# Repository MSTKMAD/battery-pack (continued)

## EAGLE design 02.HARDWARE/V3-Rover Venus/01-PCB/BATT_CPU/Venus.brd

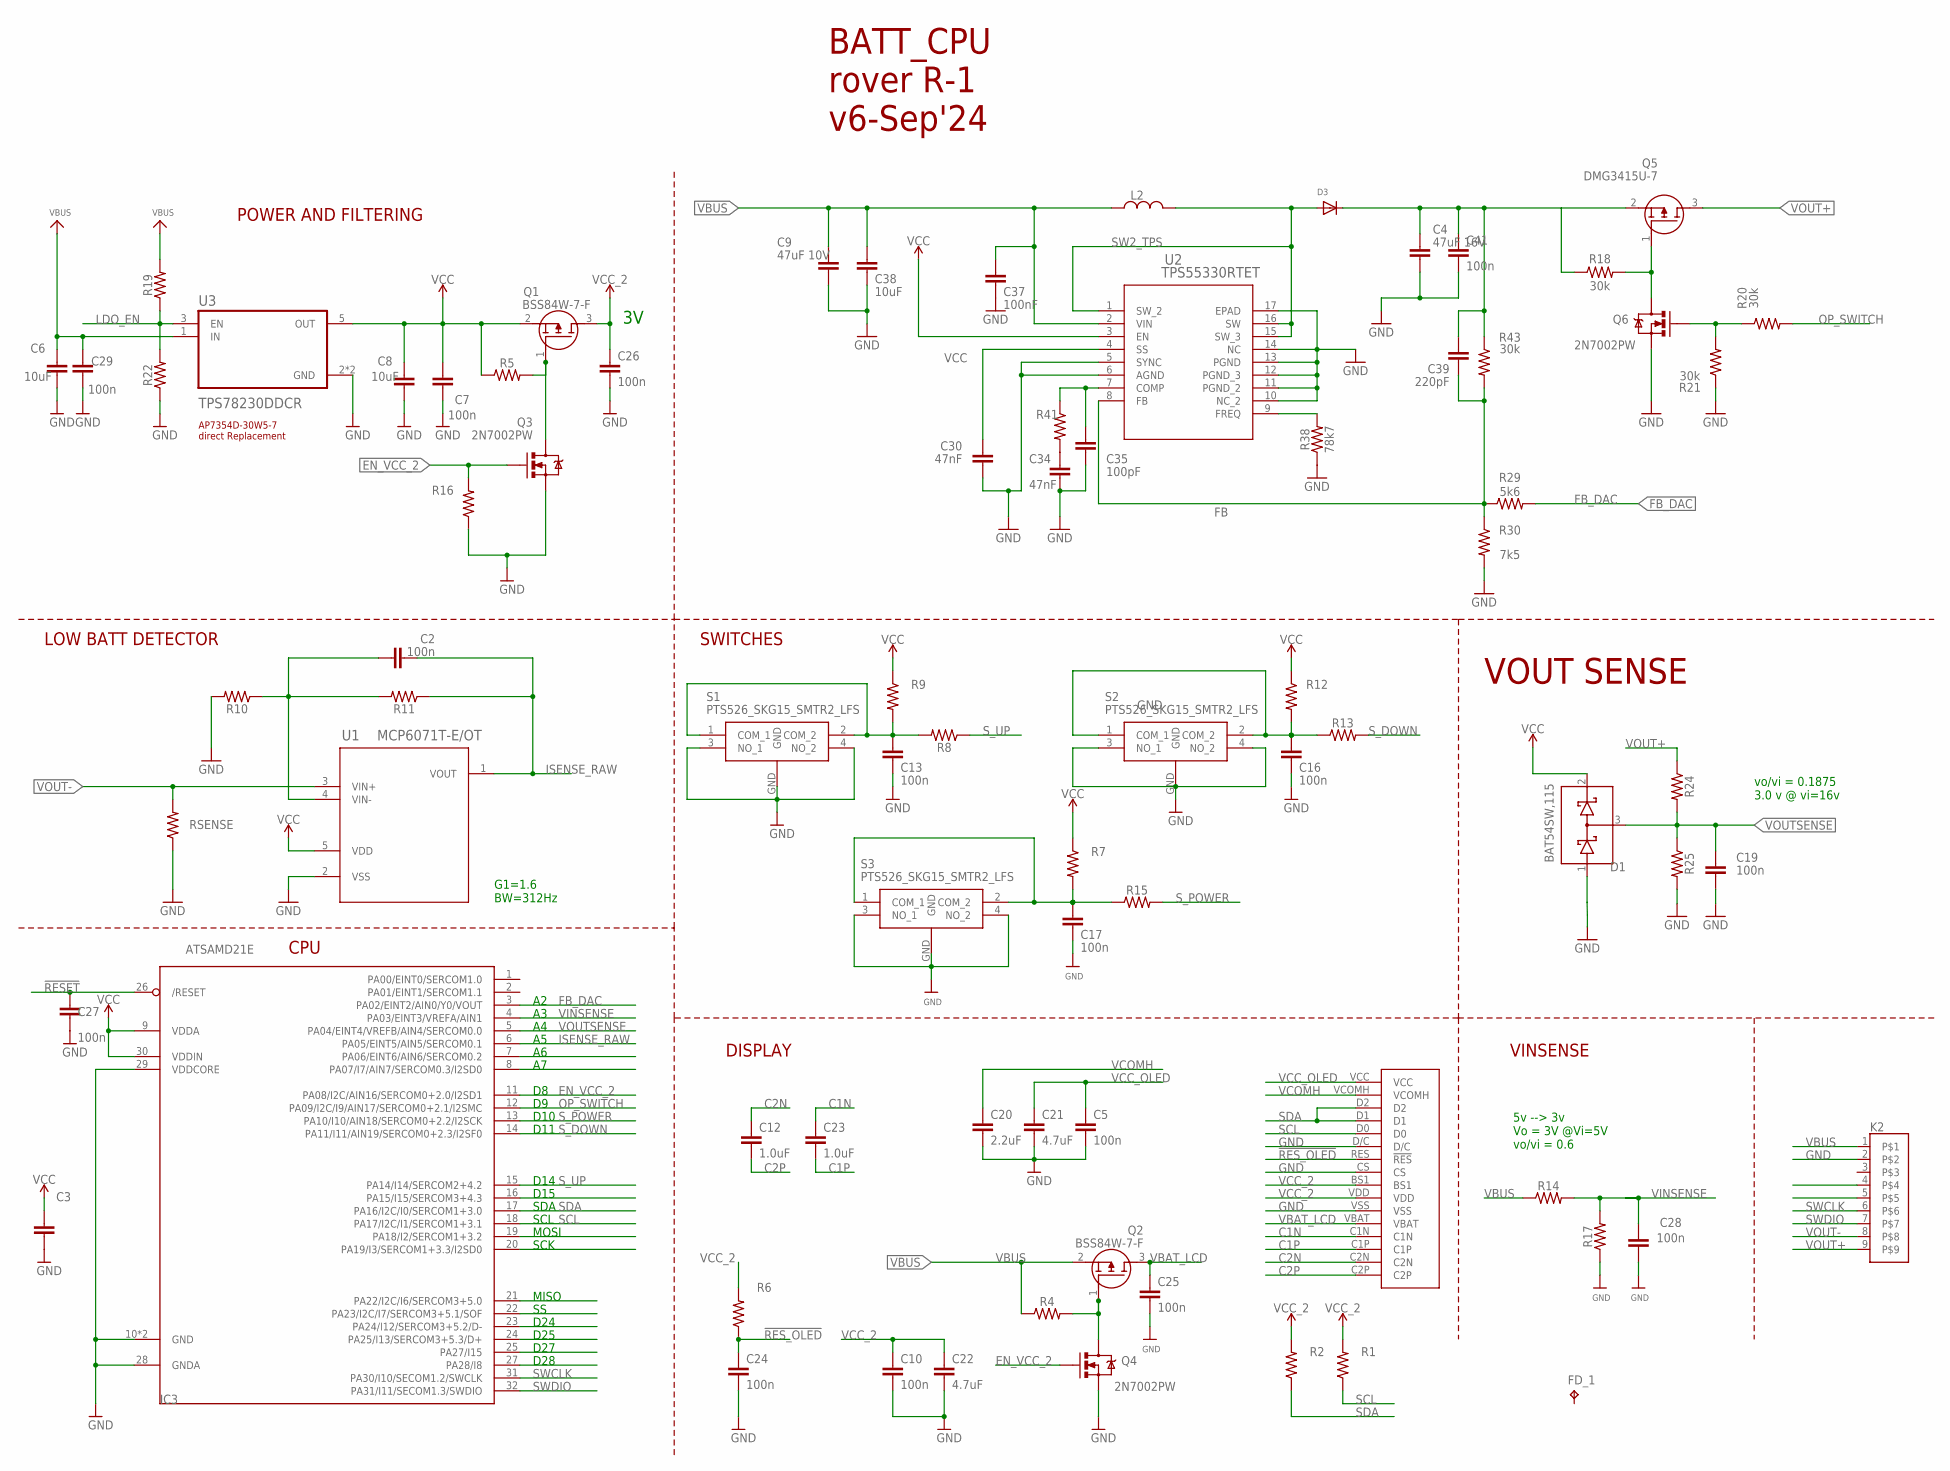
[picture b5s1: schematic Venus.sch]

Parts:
C2, C19, C41: 100n; 0603
C3, C5, C7, C10, C13, C16, C17, C24, C25, C26, C27, C28, C29: 100n; 0402
C4: 47uF 16V; CAPC3216X135
C6, C8: 10uF; 0603
C9: 47uF 10V; CAPC2012X110
C12, C23: 1.0uF; 0402
C20: 2.2uF; 0603
C21, C22: 4.7uF; 0603
C30, C34: 47nF; 0603
C35: 100pF; 0603
C37: 100nF; 0603
C38: 10uF; 0805
C39: 220pF; 0603
D1: BAT54SW,115; SOT65P210X110-3N
D3: DIODESOD-123; SOD-123
FD_1: FD_1; TP06SQ
IC3: ATSAMD21E; QFN32_5MM
K2: FLEX9_2MM
L2: L_CHIP-1206(3216-METRIC); INDC3216X190
Q1, Q2: BSS84W-7-F; SOT65P222X110-3N
Q3, Q4, Q6: 2N7002PW; SOT323
Q5: DMG3415U-7; SSM3J332RLFT
R1, R2, R4, R5, R6, R7, R8, R9, R10, R11, R12, R13, R14, R15, R16, R17, R19, R22, R24, R25, R41: 0402
R18, R20, R21, R43: 30k; 0402
R29: 5k6; 0402
R30: 7k5; 0402
R38: 78k7; 0402
RSENSE: 1206
S1, S2, S3: PTS526_SKG15_SMTR2_LFS; PTS526SKG15SMTR2LFS
U1: MCP6071T-E/OT; SOT-23-5_MC_MCH
U2: TPS55330RTET; RTE16_1P66X1P66_TEX
U3: TPS78230DDCR; SOT95P280X110-5N
U$30: 72X40_OLED; LCD_16_PINS

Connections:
!RESET: C27.1, IC3.26 (/RESET)
!RES_OLED: C24.1, R6.1, U$30.RES (!RES)
C1N: C23.1, U$30.C1N
C1P: C23.2, U$30.C1P
C2N: C12.1, U$30.C2N
C2P: C12.2, U$30.C2P
COMP_TPS: C35.2, R41.1, U2.7 (COMP)
EN_VCC_2: IC3.11 (PA08/I2C/AIN16/SERCOM0+2.0/I2SD1), Q3.1 (G), Q4.1 (G), R16.2
FB: C39.1, R29.1, R30.1, R43.2, U2.8 (FB)
FB_DAC: IC3.3 (PA02/EINT2/AIN0/Y0/VOUT), R29.2
FREQ_TPS: R38.2, U2.9 (FREQ)
GND: C3.2, C4.2, C5.2, C6.2, C7.2, C8.2, C9.2, C10.2, C13.2, C16.2, C17.2, C19.2, C20.2, C21.2, C22.2, C24.2, C25.2, C26.2, C27.2, C28.2, C29.2, C30.2, C34.1, C35.1, C37.1, C38.1, C41.2, D1.1 (A), IC3.10 (GND), IC3.28 (GNDA), IC3.29 (VDDCORE), IC3.33 (GND), K2.2, Q3.2 (S), Q4.2 (S), Q6.2 (S), R10.2, R16.1, R17.1, R21.1, R22.1, R25.2, R30.2, R38.1, RSENSE.1, S1.3 (NO_1), S1.4 (NO_2), S1.GND, S2.3 (NO_1), S2.4 (NO_2), S2.GND, S3.3 (NO_1), S3.4 (NO_2), S3.GND, U1.2 (VSS), U2.5 (SYNC), U2.6 (AGND), U2.10 (NC_2), U2.11 (PGND_2), U2.12 (PGND_3), U2.13 (PGND), U2.14 (NC), U2.17 (EPAD), U3.2 (GND), U3.4 (GND), U$30.CS, U$30.D/C, U$30.VSS
ISENSE_RAW: C2.1, IC3.6 (PA05/EINT5/AIN5/SERCOM0.1), R11.1, U1.1 (VOUT)
LDO_EN: R19.1, R22.2, U3.3 (EN)
unnamed: C17.1, R7.2, R15.1, S3.1 (COM_1), S3.2 (COM_2)
unnamed: C13.1, R8.2, R9.2, S1.1 (COM_1), S1.2 (COM_2)
unnamed: C16.1, R12.2, R13.1, S2.1 (COM_1), S2.2 (COM_2)
unnamed: Q2.1 (G), Q4.3 (D), R4.2
unnamed: C2.2, R10.1, R11.2, U1.4 (VIN-)
unnamed: Q1.1 (G), Q3.3 (D), R5.2
unnamed: Q6.1 (G), R20.1, R21.2
unnamed: Q5.1 (G), Q6.3 (D), R18.2
unnamed: C30.1, U2.4 (SS)
unnamed: C34.2, R41.2
OP_SWITCH: IC3.12 (PA09/I2C/I9/AIN17/SERCOM0+2.1/I2SMC), R20.2
SCL: IC3.18 (PA17/I2C/I1/SERCOM1+3.1), R1.1, U$30.D0
SDA: IC3.17 (PA16/I2C/I0/SERCOM1+3.0), R2.1, U$30.D1, U$30.D2
SW2_TPS: D3.A, L2.2, U2.1 (SW_2), U2.15 (SW_3), U2.16 (SW)
SWCLK: IC3.31 (PA30/I10/SECOM1.2/SWCLK), K2.6
SWDIO: IC3.32 (PA31/I11/SECOM1.3/SWDIO), K2.7
S_DOWN: IC3.14 (PA11/I11/AIN19/SERCOM0+2.3/I2SF0), R13.2
S_POWER: IC3.13 (PA10/I10/AIN18/SERCOM0+2.2/I2SCK), R15.2
S_UP: IC3.15 (PA14/I14/SERCOM2+4.2), R8.1
VBAT_LCD: C25.1, Q2.3 (D), U$30.VBAT
VBUS: C6.1, C9.1, C29.1, C37.2, C38.2, K2.1, L2.1, Q2.2 (S), R4.1, R14.1, R19.2, U2.2 (VIN), U3.1 (IN)
VCC: C3.1, C7.1, C8.1, D1.2 (C), IC3.9 (VDDA), IC3.30 (VDDIN), Q1.2 (S), R5.1, R7.1, R9.1, R12.1, U1.5 (VDD), U2.3 (EN), U3.5 (OUT)
VCC_2: C10.1, C22.1, C26.1, Q1.3 (D), R1.2, R2.2, R6.2, U$30.BS1, U$30.VDD
VCC_OLED: C5.1, C21.1, U$30.VCC
VCOMH: C20.1, U$30.VCOMH
VINSENSE: C28.1, IC3.4 (PA03/EINT3/VREFA/AIN1), R14.2, R17.2
VOUT+: K2.9, Q5.3 (D), R24.1
VOUT-: K2.8, RSENSE.2, U1.3 (VIN+)
VOUTSENSE: C19.1, D1.3 (A-C), IC3.5 (PA04/EINT4/VREFB/AIN4/SERCOM0.0), R24.2, R25.1
VSOURCE: C4.1, C39.2, C41.1, D3.C, Q5.2 (S), R18.1, R43.1

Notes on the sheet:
POWER AND FILTERING
AP7354D-30W5-7 direct Replacement
LOW BATT DETECTOR
CPU
D15
5v --> 3v Vo = 3V @Vi=5V vo/vi = 0.6
BATT_CPU rover R-1 v6-Sep'24
DISPLAY
SWITCHES
VINSENSE
G1=1.6 BW=312Hz
vo/vi = 0.1875 3.0 v @ vi=16v
VOUT SENSE
SDA
SCL
MOSI
SCK
D14
MISO
D24
D25
D27
D28
D10
D11

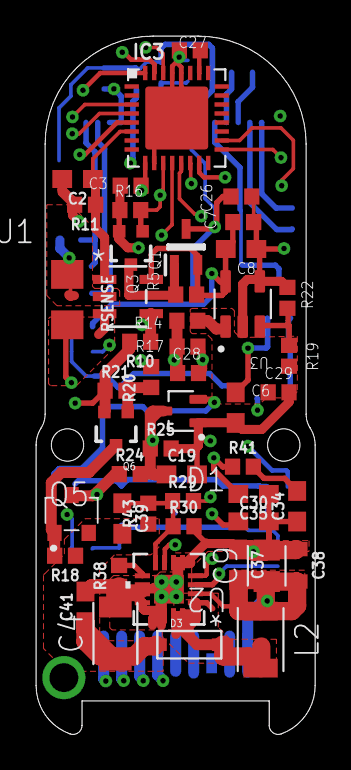
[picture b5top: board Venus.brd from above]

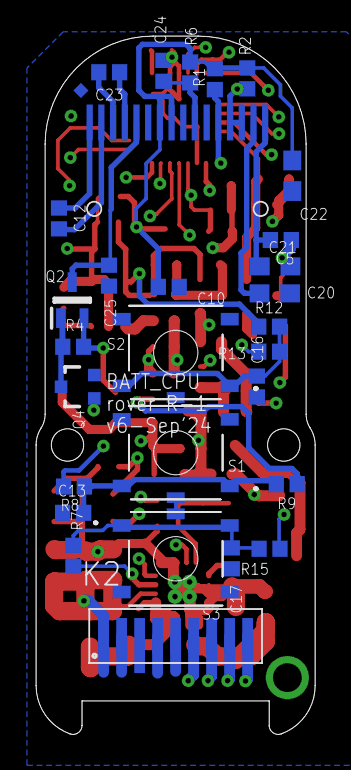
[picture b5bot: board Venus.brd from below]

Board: 4 copper layers, 15.5 x 38.8 mm, 79 parts (30 on the bottom side), 44 nets.

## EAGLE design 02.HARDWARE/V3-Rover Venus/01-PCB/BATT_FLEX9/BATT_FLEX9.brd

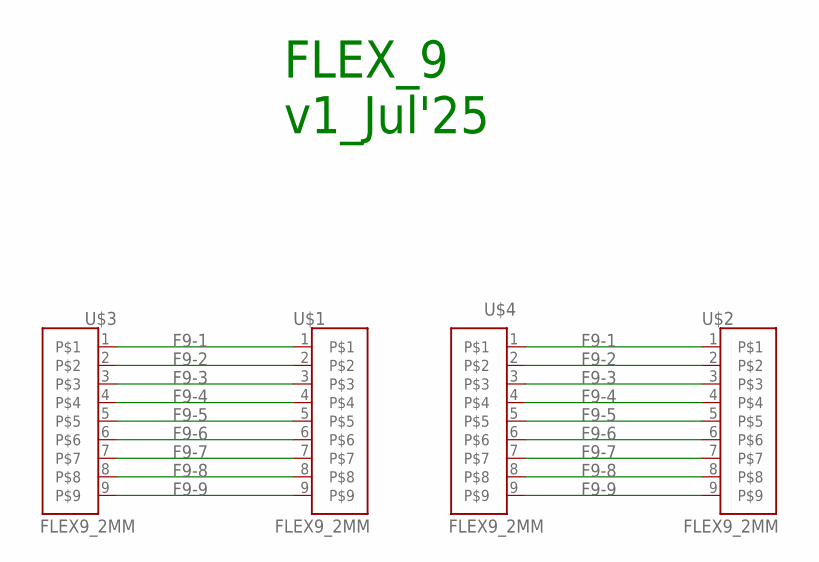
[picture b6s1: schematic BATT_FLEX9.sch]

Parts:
U$1, U$2, U$3, U$4: FLEX9_2MM

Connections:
F9-1: U$1.1, U$2.1, U$3.1, U$4.1
F9-2: U$1.2, U$2.2, U$3.2, U$4.2
F9-3: U$1.3, U$2.3, U$3.3, U$4.3
F9-4: U$1.4, U$2.4, U$3.4, U$4.4
F9-5: U$1.5, U$2.5, U$3.5, U$4.5
F9-6: U$1.6, U$2.6, U$3.6, U$4.6
F9-7: U$1.7, U$2.7, U$3.7, U$4.7
F9-8: U$1.8, U$2.8, U$3.8, U$4.8
F9-9: U$1.9, U$2.9, U$3.9, U$4.9

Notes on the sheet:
FLEX_9 v1_Jul'25

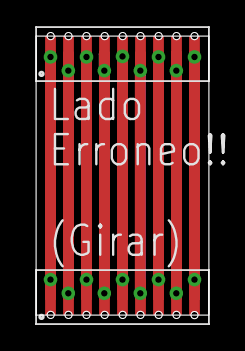
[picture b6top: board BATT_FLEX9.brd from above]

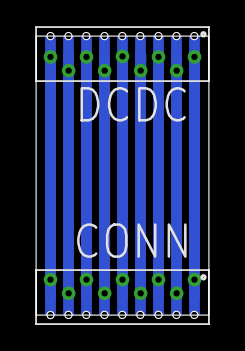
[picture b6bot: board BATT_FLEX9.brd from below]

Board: 2 copper layers, 9.6 x 15.5 mm, 4 parts (2 on the bottom side), 9 nets.

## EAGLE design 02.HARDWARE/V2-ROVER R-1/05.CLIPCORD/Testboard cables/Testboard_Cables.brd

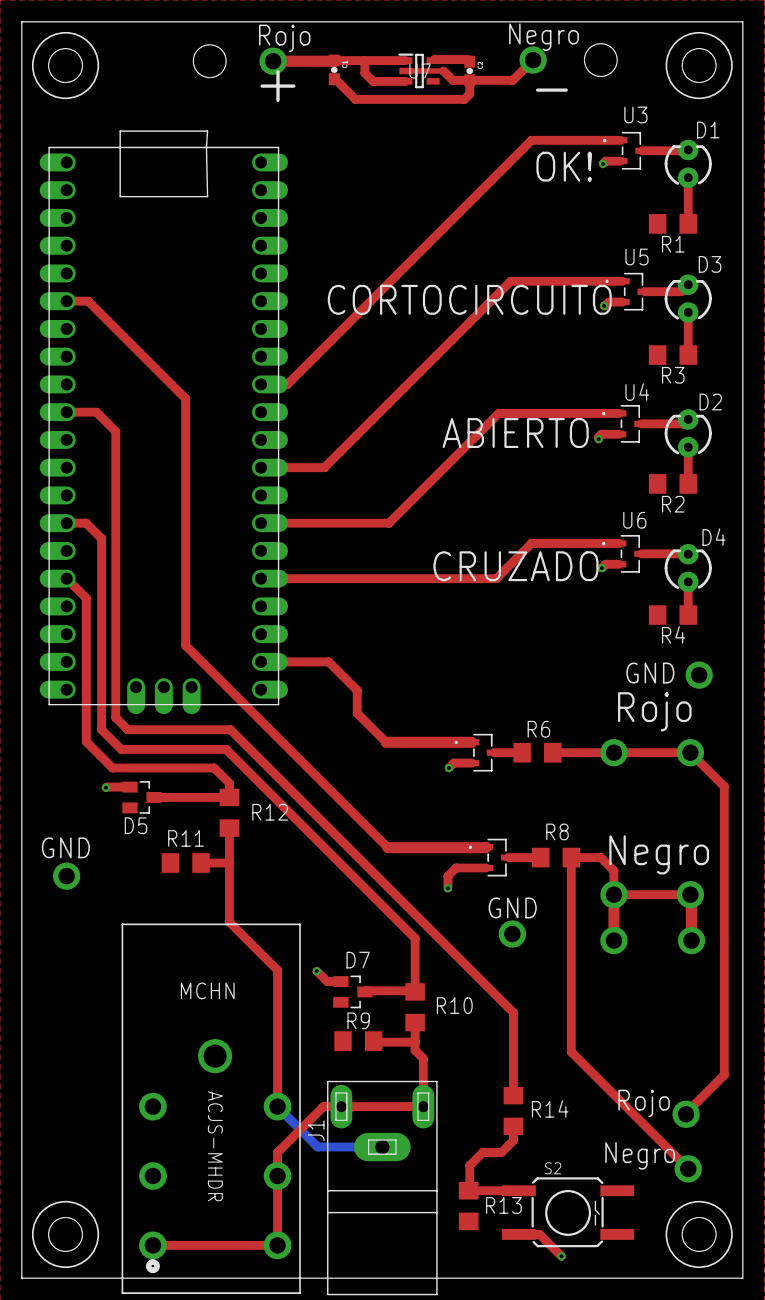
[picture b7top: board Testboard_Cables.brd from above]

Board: 2 copper layers, 65.9 x 114.9 mm, 31 parts (0 on the bottom side), 25 nets.

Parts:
C1: 2.2u; 0603-CAP
C2: 47uF 6.3V; 0603-CAP
D1, D2, D3, D4: LED_3MM
D5, D7: BAV199; SOT23
J1: PJRAN1X1U01X
MCHN: ACJS-MHDR; CONN_MHDR_AMP
R1, R2, R3, R4: 150R; 1206
R6, R8, R10, R12, R14: 100R; 1206
R9, R11, R13: 1k; 1206
S2: TAC_SW_SMD_KSC931G
U1, U2, U3, U4, U5, U6: MMUN2211LT1G; SOT-23-3_1P4X3P040_ONS
U7: AP2205-33W5-7; SOT95P282X145-5N
X1: RPI_PICO_TH

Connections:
A: U1.1, X1.GP17
B: U2.1, X1.GP4
BUTTON: R14.1, X1.GP7
CROSSED: U6.1, X1.GP19
GND: C1.2, C2.2, D5.1, D7.1, S2.3, U1.2, U2.2, U3.2, U4.2, U5.2, U6.2, U7.2, X1.GND@1, X1.GND@2, X1.GND@3, X1.GND@4, X1.GND@5, X1.GND@6, X1.GND@7, X1.GND@8
INA: J1.2, J1.3, MCHN.1, MCHN.4, MCHN.5, R9.2, R10.1
INB: J1.1, MCHN.6, R11.2, R12.1
INPUT: C1.1, U7.1, U7.3
unnamed: D1.K, U3.3
unnamed: D1.A, R1.1
unnamed: R13.1, R14.2, S2.1
unnamed: D2.K, U4.3
unnamed: D2.A, R2.1
unnamed: D3.K, U5.3
unnamed: D3.A, R3.1
unnamed: D4.K, U6.3
unnamed: D4.A, R4.1
unnamed: R6.2, U1.3
unnamed: R8.2, U2.3
OK: U3.1, X1.GP27_A1
OPEN: U4.1, X1.GP21
RA: D7.3, R10.2, X1.GP10
RB: D5.3, R12.2, X1.GP12
SHT_CRT: U5.1, X1.GP22
VCC: C2.1, D5.2, D7.2, R1.2, R2.2, R3.2, R4.2, R9.1, R11.1, R13.2, U7.5, X1.VSYS

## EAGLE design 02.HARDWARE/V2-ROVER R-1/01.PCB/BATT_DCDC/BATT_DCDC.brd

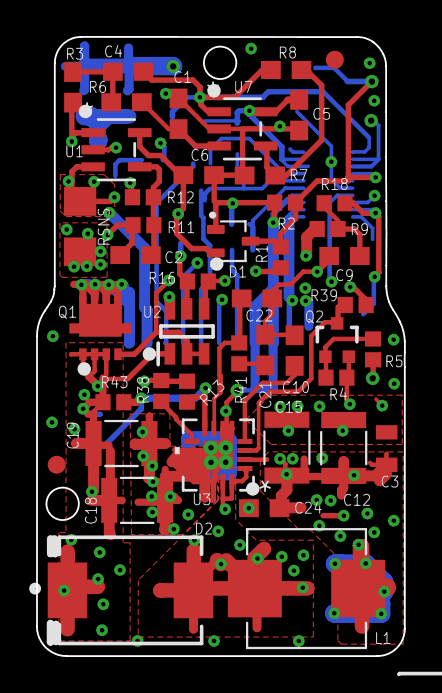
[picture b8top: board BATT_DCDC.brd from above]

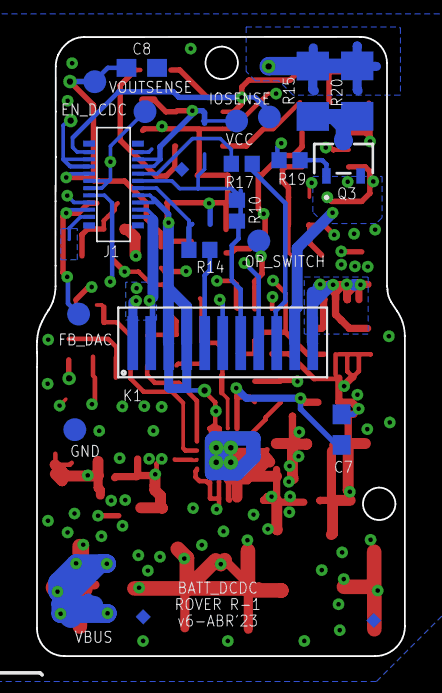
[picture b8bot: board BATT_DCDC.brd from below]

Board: 4 copper layers, 20.4 x 34.4 mm, 67 parts (22 on the bottom side), 36 nets.

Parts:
C1, C4: 1u; 0603-NO
C2, C5, C6, C8: 100n; 0603
C3: 10uF; 0805
C7: 220pF; 0603
C9: N.A.; 0603
C10, C21: 47nF; 0603
C12, C15: 47uF 16V; WCAP-CSGP_1210
C18, C19: 47uF 25V; WCAP-CSGP_1210
C22: 100pF; 0603
C24: 100nF; 0603
D1: BAT54SW,115; SOT65P210X110-3N
D2: B520C-13-F; DIOM7959X250N
EN_DCDC: TESTPAD_TPSQB1,27; TESTPAD_B1,27
FB_DAC: TESTPAD_TPSQB1,27; TESTPAD_B1,27
FD_1, FD_2, FD_3: FD_1; TP06SQ
GND: TESTPAD_TPSQB1,27; TESTPAD_B1,27
IOSENSE: TESTPAD_TPSQB1,27; TESTPAD_B1,27
J1: DF40C-20DP-0.4V_51_; DF40C-20DPA
K1: FLEX11
L1: 2.2uH - 74437346022; INDM7366X500
OP_SWITCH: TESTPAD_TPSQB1,27; TESTPAD_B1,27
Q1: NVTFS9D6P04M8LTAG; NVTFS5124PLTWG
Q2: 2N7002PW; SOT323
Q3: DMN3023L-7; SOT23-TO-236AB_NEX-L
R1: 169k; 0402
R2: 39k; 0402
R3: 2k4; 0603
R4: 100k; 0402
R5, R19: 33R; 0402
R6: 62k; 0603
R7: 4k3; 0603
R8: 36k; 0603
R9: 5k6; 0402
R10, R14, R17: 100R; 0402
R11: 5k1; 0402
R12: 8k2; 0402
R13: 7k5; 0402
R15, R20: 10R; 1206
R16: 10k; 0402
R18: 0R; 0402
R38, R39: 78k7; 0402
R41: 15k; 0402
R43: 30k; 0402
RSNS: 100mR; 1206
U1, U7: MCP6071T-E/OT; SOT-23-5_MC_MCH
U2: LM5114BMF_NOPB; SOT95P280X145-6N
U3: TPS55330RTET; RTE16_1P66X1P66_TEX
U$1, U$2: FIDUCIAL""; FIDUCIAL_1MM
VBUS: TESTPAD_TPSQB1,27; TESTPAD_B1,27
VCC: TESTPAD_TPSQB1,27; TESTPAD_B1,27
VOUTSENSE: TESTPAD_TPSQB1,27; TESTPAD_B1,27

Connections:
!RESET: J1.8, R17.1
COMP_TPS: C22.2, R41.1, U3.7
EN_DCDC: EN_DCDC.TP, J1.9, J1.11, R5.2
EN_TPS: Q2.3, R39.2, U3.3
FB: C7.1, R9.1, R13.1, R43.2, U3.8
FB_DAC: FB_DAC.TP, J1.17, R18.2
FREQ_TPS: R38.2, U3.9
GND: C1.2, C3.1, C5.2, C6.2, C8.2, C9.2, C10.2, C12.1, C15.1, C18.1, C19.1, C21.1, C22.1, C24.1, D1.1, GND.TP, J1.2, J1.14, J1.16, K1.3, K1.4, Q2.2, R2.2, R4.1, R7.2, R12.2, R13.2, R16.2, R38.1, RSNS.1, U1.2, U2.4, U3.5, U3.6, U3.10, U3.11, U3.12, U3.13, U3.14, U3.17, U7.2
IOSENSE: C4.2, IOSENSE.TP, J1.1, R8.1, U7.1
ISENSE_RAW: C2.1, R3.2, R11.1, U1.1
unnamed: C2.2, R11.2, R12.1, U1.4
unnamed: R7.1, R8.2, U7.4
unnamed: C4.1, R3.1, R6.2
unnamed: Q2.1, R4.2, R5.1
unnamed: C1.1, R6.1, U7.3
unnamed: K1.8, R10.2
unnamed: Q3.3, R15.1, R20.1
unnamed: Q1.4, R19.1, U2.2, U2.3
unnamed: K1.10, R17.2
unnamed: K1.5, R14.2
unnamed: C9.1, R9.2, R18.1
unnamed: Q3.1, R19.2
unnamed: C10.1, U3.4
unnamed: C21.2, R41.2
OP_SWITCH: J1.3, J1.5, OP_SWITCH.TP, R16.1, U2.5
RXI: J1.15, K1.9
SW2_TPS: D2.A, L1.2, U3.1, U3.15, U3.16
SWCLK: J1.10, R10.1; also elsewhere on the board
SWDIO: J1.12, R14.1; also elsewhere on the board
TXO: J1.13, K1.7
VBUS: C3.2, C12.2, C15.2, C24.2, J1.18, J1.20, K1.1, K1.2, L1.1, U3.2, VBUS.TP
VCC: C5.1, C6.1, D1.2, J1.4, J1.6, R39.1, U1.5, U7.5, VCC.TP; also elsewhere on the board
VOUT+: K1.12, Q1.5, Q1.6, Q1.7, Q1.8, Q1.9, Q1.10, Q1.11, R1.1, R15.2, R20.2
VOUT-: K1.11, Q3.2, RSNS.2, U1.3
VOUTSENSE: C8.1, D1.3, J1.7, R1.2, R2.1, VOUTSENSE.TP
VSOURCE: C7.2, C18.2, C19.2, D2.C, Q1.1, Q1.2, Q1.3, R43.1, U2.1, U2.6

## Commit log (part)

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2023-01-27 Ajuste del Debug via puerto Serie
2023-01-27 Fix del timer del boton central en la interrupcion del despertar.
2023-01-27 enviado a PCBWAY
2023-01-27 close #29
2023-01-31 Test de los avisos de los errores
2023-01-31 codigo de verificacion de fabricacion de las placas de testeo.
2023-02-01 Calculo de los valores del DAC de 12 bits
2023-02-01 Mensajes de aviso de errores. close #31
2023-02-09 Añadimos el clip de thunder al repositorio
2023-02-10 Version 1 PCB JACK
2023-02-15 Close issue #33
    Nuevo diseño para conector de Amphenol
2023-02-20 codigo de testeo para la fase de produccion version 1
2023-02-24 Cierra el issue #38
    Pin de VO+ desplazado
2023-02-27 close #36
2023-02-27 close #35
2023-03-06 Funcion de Debugg
2023-03-06 close #34
2023-03-06 Test Mode. Actualizacion de la EEPROM
2023-03-17 Close #43
2023-03-17 Ajuste del umbral de la proteccion de cortocircuito
    tras realizar una serie de pruebas se decide bajar de 3A a 1,9A.
    Al realizar un corto franco se observa que la batería mide cerca de 2A.
2023-03-17 Close #40
2023-03-17 Ajuste del modo test.
    - Corrección de la salida del modo test para que todos los flags tengan el valor correcto.
    - Se añade comprobación del sensado de corriente y voltaje por pantalla,
    - Modificación de las velocidades de los trenes de pulso del Enable y del OP swtich.
2023-03-17 Cambio de nombre de la Bom del sistema
2023-03-17 Actualizacion parcial de librerias
2023-03-17 documentación de Testeo
2023-03-17 Auto stash before rebase of "refs/heads/develop"
2023-03-21 Cambio de dinamico a fijo los valores de sensado druante el test
    Para poder realizar un logeo claro y sencillo se decide que una vez se realice la verificación, el valor se quede estático.
    Adicionalmente se aumentan las variables de uint16 a uin32 para evitar el rebosamiento durante la verificación.
2023-03-21 Close #45
    Se detecta el fallo al intentar comunicarse por I2C con la pantalla cuando esta no esta correctamente alimentada tras el despertar.
    Se incluye una inicialización al despertar.
2023-03-22 Incorporacion de carpeta GFX modificada
2023-04-10 Ajuste de la posicion del numeo de serie en memoria
2023-04-12 Close #37
2023-04-13 Ajuste del incremento del modo boost
    Se decide ajustar a 0.3v el aumento que supone el modo boost.
    La linea de tensión en mas corta que en la MK y por tanto no es necesario un incremento tan grane
2023-04-17 Ajuste del WachtDog en el Naming
2023-04-25 Correccion protecciones close#44
    Se decide modificar el funcionamiento de las protecciones para ajustar al ciclo de programa y controlar los tiempos desde la construcción del Health Monitor exclusivamente.
2023-04-25 Libreria de Memoria RAM
2023-04-25 Inclusion del puerto serie en alguos puntos
    Se cierra el puerto serie para agilizar el ciclo de programa
2023-04-25 Close #51
2023-04-25 Close #24
2023-05-02 Cambio del control de tiempo de activacion del LOW BATT
2023-05-05 Close #55
    Solucion del error por Undervoltage.
2023-05-16 Introducción de Supervisor de tensión con control de RESET 2,63.
2023-05-16 Inclusion de Tests Pads
2023-05-16 Serigrafia de version 3
2023-05-16 Actualizacion BOM v6
2023-05-16 Cambio en el encapsulado de 4 Resistencias para evitar que salten en el soldado.
2023-05-16 Produccion 2 - Mecanica
    Actualizacion de la ficheros de mecanica para la segunda produccion
2023-05-17 v7
    Issue #49, #59, #60 y #63
2023-05-17 Cierra issue #63 #59 #49 #32 #60
2023-05-18 SETI Batch_2
    Generacion de GERBER
    Generacion de MOUNTSMD Files
2023-05-18 fichero movido a GERBER directory
2023-05-18 HISTORY updated
2023-05-18 Se crea el folder de PRODUCCION
    para tener identificado todos los ficheros enviados a proveedores y fabricantes
2023-06-01 Fix Errors.
    Errores en los condensadores. C2 por C6.
    Errores en R20 y R21. Los valores estaban intercambiados.
2023-06-01 Diseño Clipcord PCB
2023-06-01 Tabla potencia-tiempo
2023-06-22 Correcion de la granularidad del power use
2023-08-02 Ajuste de tiempos del test DCDC
2023-08-02 Modo Nitro version inicial
2023-08-02 Stop Tracking Produccion folder
2023-08-03 Fix values en Test DCDC
    Ajuste de los valores de verificacion de corriente en el Test 3 de la DCDC
2023-08-21 primera version
2023-08-21 Enviado a Adam Darklord
    Util para post o para demostraciones
2023-08-24 se cambia la forma exterior (WIP)
    No esta terminado
2023-08-25 Placa de Conexiones DCDC Pogo v2 + Placas Pinza
2023-08-25 PCBs Testbench DK Motor+Optos
2023-09-02 Pedido JLCJBC - 1er Pedido
2023-09-05 Cambios en libreria DCDC y adaptacion del codigo B2 al uso de PWM
    Se incluyen las carpetas de testeo y de codigos de ejemplo. Ademas de la libreria usada
2023-09-11 Issue #72
2023-09-19 Cambio del Nitro.
    El nitro por encima de 5v es una escalera hasta 4 voltios por encima del voltaje objetivo.
2023-09-20 Commit anused PIN.
2023-09-20 Adaptacion placa CONECTORES a Universal
2023-09-21 Cambios menores antes de pedido
2023-09-21 Cambios menores antes de pedido + GERBER
2023-09-21 Cambios menores en esquematico
    Se corrigen valores de Resistencias para PWM
    Actualizado el titulo del esquematico
    Limpieza general
2023-09-21 GERBER para pedido SETI
2023-09-22 Codigo principal recuperado
2023-09-25 Revisión BOM previa envio SETI
2023-09-26 Fix error
    Solucion de inconsistencia de valores entre el BRD y el SCH
2023-09-26 Revision antes de enviar a SETI 3ra produccion
    Se actuliza la columna NEW
2023-09-26 Revision antes de envio SETI 3ra produccion - SEP-23
2023-09-26 Cambio de diseño de las placas de la univerasl
    v2
2023-09-26 Ajuste del ancho del orificio del pogo
2023-09-29 Modificaciones en area de soldadura para que haya mas superficie (WIP)
2023-09-29 Revert "Activacion del Nitro Por defecto"
    This reverts commit 9dda1e81689fddb32595ea665b642b7bc7b6e64d.
2023-10-02 Modificacion v3 Pogo pin universal
2023-10-04 Produccion de GERBER para pedido JLCPCB W202310041757817
2023-10-25 Ajustes PCBs
    Cambio en el pcb de cheyenne para que entre en el adapatador de la universal.
    Cambio en el pcb del pogo para que se ajuste mejor a los adaptadores de la universal
2023-10-27 generacion de GERBER para pedido JLCPCB
2023-10-31 Version Low Voltage v1
2023-11-09 Actualizacion de la BOM
    Esquema de resistencia de balastro,
2023-11-15 Revision y GERBER antes de enviar a SETI
    Ficheros para produccion 4ª de SETI (Dan Kubin y PMU compatible
2023-11-16 Inclusion de la feature configuracion de nitro en la version Low Voltage
2023-11-16 Inicio de version
2023-11-16 Se deja de trackear esta carpeta
2023-11-16 Carpeta con proyecto Flash para desarrollo
2023-11-22 Listado pruebas regresion ante cambios menores de version
2023-11-22 Fix errors
    Cambios para facilitar el uso del script para comprobaciones del PWM.
2024-01-29 1º Version Rampas mejora de arranque
    Se introduce una rampa para el arrancado cuando el nitro esta desactivado
2024-01-29 Fix error
    Por el desarrollo del ciclo de programa, ocurria que la salida se activaba con el voltaje deseado antes de que se realizara el arranque.
2024-01-30 Excel de control de Versiones de Sistema
2024-01-30 Integracion rampa de arrancado Sin Nitro
2024-01-30 Fix Errors
    Por el desarrollo del ciclo de programa, ocurria que la salida se activaba con el voltaje deseado antes de que se realizara el arranque.
2024-01-30 Versiones 3040 y 3004
2024-01-30 Nomenclatura de versiones
2024-01-30 Libreria pantalla 0916
2024-02-07 Modulacion del voltaje de salida por Duty y por Voltaje
2024-02-08 Documento de control de compatibilidades
2024-02-09 v1PCB Adaptador Fk Irons
2024-02-13 Cierra issue #74
    Modificaciones para que el estaño no fluya por las vias a la cara vista
2024-02-16 Cambios en serigrafia
2024-02-27 Modificaciones para solucionar issue #75 (WIP)
    Todavia pendiente de hacer mas cambios
2024-02-27 close issue #75
2024-02-29 Cierra issue #76 - Listo para pedido a PCBWAY
    Mejoras para que no toque con mecanica
    Mejora para evitar que se desuelden los cables por calentamiento del conecgtor
2024-03-14 Issue #77
2024-04-08 gitflow-feature-stash: CheyenneStep
2024-04-09 Gitignore update. .build folders
2024-04-10 Actualizacion de la version por el hotfix
2024-04-10 volcado de memoria en inerscion de pila
2024-04-10 Eliminacion temporal del Watchdog de todas las versiones y de todas las librerias
    Quedan supeditadas a una variables de definicion.
2024-04-10 Update git ignore /build
2024-04-17 Sketch testeo de PWM, Duty y Voltaje de la PWM para PMU
2024-04-17 Documentos de Calibracion del DCDC con el DAC
2024-04-29 Cambios
2024-05-13 Updae Gitignore
2024-05-13 Cambio en el sistema de nomenclatura de versiones
2024-05-13 Sustitucion de B2 por B2-RCA
2024-05-17 Clipcord L v1. Creacion
    Creacion del modelo de clipcord para el modelo L. Heredado de la version 2 del modelo M
2024-05-17 Fix Error.
    La variable al ser de 8 bits, no se podían almacenar versiones por encima de 256.
2024-05-28 Test Codes
2024-05-28 Actualizacion de version
2024-05-29 Fix Error. Si daba Empt bateris no se podia apagar manualmente
2024-05-29 Version de Sistema Actualizada
2024-06-05 Revert "Merge pull request #84 from MSTKMAD/develop"
    This reverts commit 96fc117d3460fb5d771273194348358b85af1598, reversing
    changes made to 9bb4215ab554844daf6eea25f914757804df500a.
2024-06-05 Close #80
2024-06-05 Version Update Cheyenne SW
2024-06-17 Connector Version named in HW
2024-07-23 Reconocimiento de producciones HW de forma visual
2024-07-29 PCB FK DIANA v2. se estrecha un poco el pcb pasra entrar mejor en la mecanica
2024-09-05 Version Inicial del Tester de Cables.
2024-09-09 Conflicto en la atención a error con el aviso de low battery, #85
2024-09-09 La bateria da salida estando apagada. Close #83
2024-09-09 MOSFET de Salida cerrado permanentemente #87.
2024-09-09 Fallo en el sensado de VIN antes del apagado.
2024-09-17 Connectores. Se añaden PADs para señales de comunicacion.
2024-09-17 Union de salidas digitales a SWD. CPU
2024-09-17 Se añaden 2 anillos mas
2024-09-17 Retrofit a valores de tamaños adecuados a la mecanica. POGO
2024-09-17 Placa con 4 pines.v1
2024-09-18 eliminicacion B2 (deprecated)
2024-09-23 Fix minor issues.
2024-10-21 Actualiuzacion de Resistencias y Pedido a Seti
2024-10-21 Codigo Verificacion de Test Cable
2024-11-20 Ajuste de Voltaje para trbajar por DCDC hasta 4v
2024-11-20 Cambio para albergar Versiones por encima de 255
2024-11-20 Archivos de Testeo
2024-11-20 Hotfix BOM CPU
2025-02-10 Prueba de concepto con señales data e ID
2025-02-11 Universal bulk files
2025-02-21 Genaracion de .fab para seti
2025-03-11 Version 1.0 con PID incluido y funcion
    Se activa solo con RUN, pero se adapta cuando se sube y baja el voltaje.
2025-03-17 Version PID v3
    Añadido control visual de la barra de potencia como idicador de activacion del PID
2025-04-10 Modo Vanta includo
2025-04-21 Modificacion del estado por defecto del nitro en TODAS las versiones de ROVER
2025-05-09 Cambio de version del display del modo mthr fckr
2025-05-15 pid and Display Hz
2025-07-24 Test SamdE
2025-07-24 librerias neopixel y dotstar
2025-07-24 Primera version enviada a PCBWAY
2025-08-01 MErge
2025-09-23 Cradle Venus
2025-09-29 Creacion del la version VantaBlack
2025-09-29 Cambios DCDC
2025-09-29 Salida a produccion de VantaBlack v500
2025-09-29 VantaBlack Update
2025-10-06 Fix bug. Fallo displayHZ
    Se estaban mostrando los HZ correspondientes al motor de 9v, cuando la Vantablack lleva el motor de 6v.
2025-11-27 Libreria Tiny Pixel
2025-11-27 Grip design v1
2025-11-27 schema de attiny16
2025-12-16 Cradle Update
2026-01-07 Gestion salida y opcion en menu
    SE importa la gestion del switch de salida del modelo DK.
    Ademas se añade el manejo del menu para tener 2 opcion. Queda pendiente decidir si meter flecha o no y la inclusion de la variable en la memoria EEPROM
2026-01-07 Create Kora Software
2026-01-14 Documentacion del Codigo de la Universal y Librerias principales
2026-01-14 Documentacion Codigo.Vanta Black
2026-01-14 Documentacion Codigo Cheyenne
2026-01-14 Documentacion Codigo KORA
